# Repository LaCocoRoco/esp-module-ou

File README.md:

# Operating Unit

Portable operating panel with touch buttons.

## Quick Guide

1. Order PCB by uploading the [Gerber File](pcb/cam/esp-module-ou.zip) to [JLCPCB](https://jlcpcb.com/).
2. Order Parts by uploading the [BOM File](pcb/bom/esp-module-ou.csv) to [LCSC](https://www.lcsc.com/bom).
3. Build PCB by placing components as visualized in the [BOM Viewer](https://htmlpreview.github.io/?https://github.com/LaCocoRoco/esp-module-ou/blob/main/pcb/bom/esp-module-ou.html).
4. Download & Install [Git](https://git-scm.com/), [CP210x Driver](https://www.silabs.com/developers/usb-to-uart-bridge-vcp-drivers?tab=downloads) and [VSCode](https://code.visualstudio.com/) with [PlatformIO](https://platformio.org/) Extension.
5. Clone the Repository `git clone --recursive https://github.com/LaCocoRoco/esp-module-ou.git`.
6. With PlatformIO `Upload Filsystem Image` & `Upload & Monitor ` to your board.

## Module Modes

Modes can be changed by pressing the mode button.  
An audio signal will provide feedback for the active mode.  
Holding the mode button for more than two seconds will clear the module.

### Low Power Mode

- Feedback with one audio signal
- All web functionality is disabled
- Device will enter deep sleep when inactive
- Battery lifetime of several months

### Hybrid Mode

- Feedback with two audio signals
- All web functionality is disabled
- Device will enter deep sleep when battery voltage is below 3.8V
- Battery lifetime of several days

### Web Mode

- Feedback with three audio signals
- All web functionality is enabled
- Battery lifetime of several hours

## Importend

All modules have three different modes: Web Mode, Hybrid Mode, and Low Power Mode.  
The Wi-Fi can be configured as either Access Point or Station Mode.  
However, due to the use of the EspNow protocol for communication, there are some restrictions.

### Modules Set Up as Access Points (Default):

- All modes work without any restrictions.

### Modules Set Up in Station Mode:

- Web Mode works without any restrictions.
- Low Power Mode and Hybrid Mode only work if the Wi-Fi network is set to a **fixed channel**.

### Modules Set Up in Access Point or Station Mode:

- All modes only work if the Wi-Fi network is set to **channel 1**.

## Explanation

The main goal of this project was to avoid reliance on any infrastructure. For configuration, neither an application nor an existing Wi-Fi network is necessary. All modules can be accessed via the corresponding SSID in Access Point Mode or via hostname in Station Mode. However, there are some trade-offs:

To reduce power consumption in Low Power Mode, the module does not establish a direct network connection. It only broadcasts data to the specified receiver. In Station Mode, the network may change the Wi-Fi channel occasionally. Connecting to the network to receive this information would significantly increase uptime.

An alternative approach to this problem would be to scan for the receiver and request the channel. However, this has additional drawbacks:

- Scanning for this information takes some time (though less compared to connecting to a Wi-Fi network).
- It is difficult to distinguish whether a transmission failure is due to the wrong channel or a general network issue.
- Continuously requesting this information until a response is received would quickly add to the uptime and increase power consumption.

This is the reason why the relevant points must be considered mentioned in the [Importand](#importend) section.

## Reference

- [VSCode](https://code.visualstudio.com/) - Lightweight code editor.
- [PlatformIO](https://platformio.org/) - Embedded software development gateway.
- [Autodesk Fusion 360](https://www.autodesk.com/products/fusion-360) - Design and manufacturing software for CAD, CAM, CAE, and PCB.
- [Autodesk Eagle](https://www.autodesk.com/products/eagle) - Electronic design automation software for printed circuit boards.
- [JLCPCB](https://jlcpcb.com/) - Reasonably priced PCB manufacturer.
- [LCSC](https://www.lcsc.com/) - Supplier for a wide selection of electronic components.
- [CP210x Driver](https://www.silabs.com/developers/usb-to-uart-bridge-vcp-drivers?tab=downloads) - USB to UART Driver for uploading codebase.
- [InteractiveHtmlBom](https://github.com/openscopeproject/InteractiveHtmlBom) - Bill of materials listing to visually search for components and their placements.

## Preview

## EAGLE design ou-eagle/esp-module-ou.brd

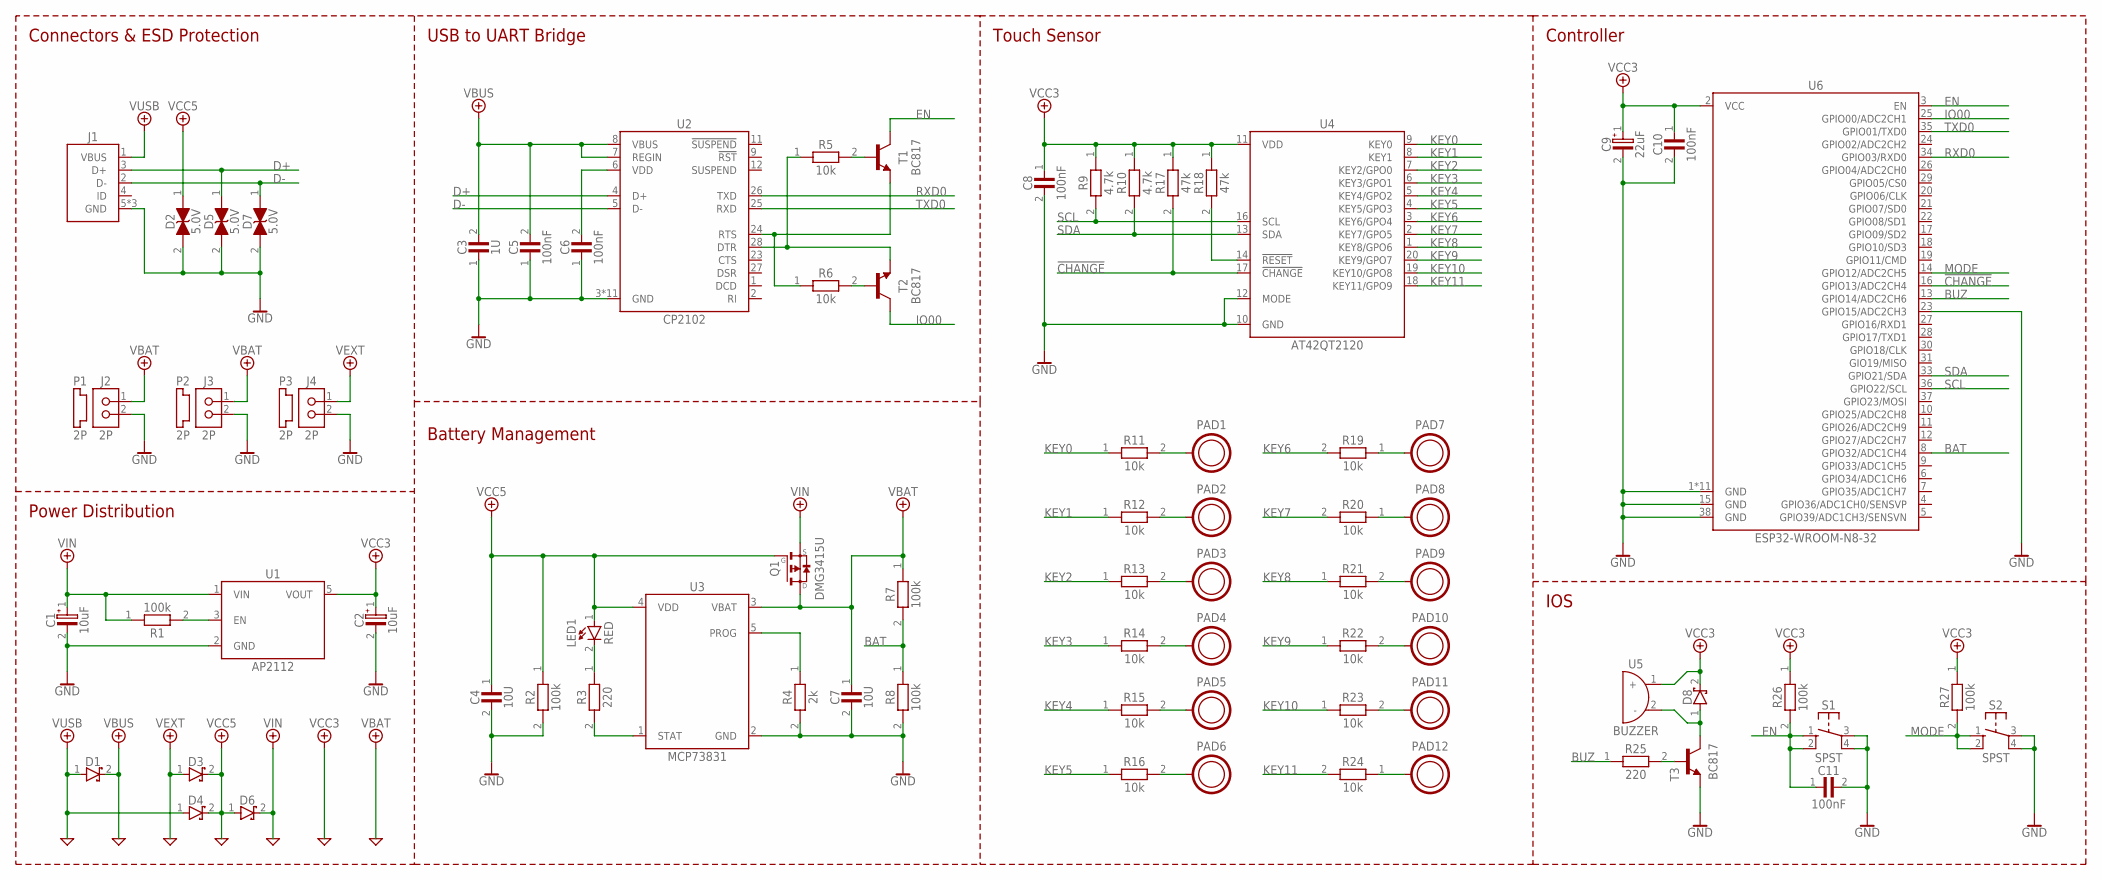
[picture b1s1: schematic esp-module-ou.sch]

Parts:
C1, C2: 10uF; I1206-M3216-D
C3: 1U; I0805-M2012-C
C4, C7: 10U; I0805-M2012-C
C5, C6, C8, C10, C11: 100nF; I0805-M2012-C
C9: 22uF; I1206-M3216-D
D1, D3, D4, D6, D8: 30V; SOD-323
D2, D5, D7: 5.0V; SOD-523
J1: USB-A-MICRO-TOP
J2, J3, J4: 2P; JST-S2B-PH-SM4-TB
LED1: RED; I0805-M2012-D
P1, P2, P3: 2P; CONNECTOR-DEFAULT
PAD1, PAD2, PAD3, PAD4, PAD5, PAD6, PAD7, PAD8, PAD9, PAD10, PAD11, PAD12: QTOUCH
Q1: DMG3415U; SOT-23-3
R1, R2, R7, R8, R26, R27: 100k; I0805-M2012-R
R3, R25: 220; I0805-M2012-R
R4: 2k; I0805-M2012-R
R5, R6, R11, R12, R13, R14, R15, R16, R19, R20, R21, R22, R23, R24: 10k; I0805-M2012-R
R9, R10: 4.7k; I0805-M2012-R
R17, R18: 47k; I0805-M2012-R
S1, S2: SPST; SMD-SW-4
T1, T2, T3: BC817; SOT-23-3
U1: AP2112; SOT-25-5
U2: CP2102; QFN-28
U3: MCP73831; SOT-23-5
U4: AT42QT2120; TSSOP-20
U5: BUZZER; SMD-BUZZER
U6: ESP32-WROOM-N8-32; ESP32-WROOM-32

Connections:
!CHANGE: R17.2, U4.17 (!CHANGE), U6.16 (GPIO13/ADC2CH4)
!RESET: R18.2, U4.14 (!RESET)
APEN: R1.2, U1.3 (EN)
BAT: R7.2, R8.1, U6.8 (GPIO32/ADC1CH4)
BUZ: R25.1, U6.13 (GPIO14/ADC2CH6)
BZB: R25.2, T3.1 (B)
BZC: D8.1 (A), T3.3 (C), U5.2 (-)
D+: D5.1 (A), J1.3 (D+), U2.4 (D+)
D-: D7.1 (A), J1.2 (D-), U2.5 (D-)
DTR: R5.1, T2.2 (E), U2.28 (DTR)
DTRT: R5.2, T1.1 (B)
EN: C11.1, R26.2, S1.1, S1.2, T1.3 (C), U6.3 (EN)
GND: C1.2 (-), C2.2 (-), C3.1, C4.2, C5.1, C6.1, C7.2, C8.2, C9.2 (-), C10.2, C11.2, D2.2 (C), D5.2 (C), D7.2 (C), J1.5 (GND), J1.6 (GND), J1.7 (GND), J2.2, J3.2, J4.2, R2.2, R4.2, R8.2, S1.3, S1.4, S2.3, S2.4, T3.2 (E), U1.2 (GND), U2.3 (GND), U2.29 (GND), U2.30 (GND), U2.31 (GND), U2.32 (GND), U2.33 (GND), U2.34 (GND), U2.35 (GND), U2.36 (GND), U2.37 (GND), U2.38 (GND), U3.2 (GND), U4.10 (GND), U4.12 (MODE), U6.1 (GND), U6.15 (GND), U6.23 (GPIO15/ADC2CH3), U6.38 (GND), U6.39 (GND), U6.40 (GND), U6.41 (GND), U6.42 (GND), U6.43 (GND), U6.44 (GND), U6.45 (GND), U6.46 (GND), U6.47 (GND), U6.48 (GND)
IO00: T2.3 (C), U6.25 (GPIO00/ADC2CH1)
KEY0: R11.1, U4.9 (KEY0)
KEY1: R12.1, U4.8 (KEY1)
KEY2: R13.1, U4.7 (KEY2/GPO0)
KEY3: R14.1, U4.6 (KEY3/GPO1)
KEY4: R15.1, U4.5 (KEY4/GPO2)
KEY5: R16.1, U4.4 (KEY5/GPO3)
KEY6: R19.2, U4.3 (KEY6/GPO4)
KEY7: R20.2, U4.2 (KEY7/GPO5)
KEY8: R21.1, U4.1 (KEY8/GPO6)
KEY9: R22.1, U4.20 (KEY9/GPO7)
KEY10: R23.1, U4.19 (KEY10/GPO8)
KEY11: R24.2, U4.18 (KEY11/GPO9)
MODE: R27.2, S2.1, S2.2, U6.14 (GPIO12/ADC2CH5)
PAD00: PAD1.1, R11.2
PAD01: PAD2.1, R12.2
PAD02: PAD3.1, R13.2
PAD03: PAD4.1, R14.2
PAD04: PAD5.1, R15.2
PAD05: PAD6.1, R16.2
PAD06: PAD7.1, R19.1
PAD07: PAD8.1, R20.1
PAD08: PAD9.1, R21.2
PAD09: PAD10.1, R22.2
PAD10: PAD11.1, R23.2
PAD11: PAD12.1, R24.1
PROG: R4.1, U3.5 (PROG)
RTS: R6.1, T1.2 (E), U2.24 (RTS)
RTST: R6.2, T2.1 (B)
RXD0: U2.26 (TXD), U6.34 (GPIO03/RXD0)
SCL: R9.2, U4.16 (SCL), U6.36 (GPIO22/SCL)
SDA: R10.2, U4.13 (SDA), U6.33 (GPIO21/SDA)
STAT: R3.2, U3.1 (STAT)
STATLED: LED1.2 (C), R3.1
TXD0: U2.25 (RXD), U6.35 (GPIO01/TXD0)
VBAT: C7.1, J2.1, J3.1, Q1.3 (D), R7.1, U3.3 (VBAT)
VBUS: C3.2, C5.2, D1.2 (C), U2.7 (REGIN), U2.8 (VBUS)
VCC3: C2.1 (+), C8.1, C9.1 (+), C10.1, D8.2 (C), R9.1, R10.1, R17.1, R18.1, R26.1, R27.1, U1.5 (VOUT), U4.11 (VDD), U5.1 (+), U6.2 (VCC)
VCC5: C4.1, D2.1 (A), D3.2 (C), D4.2 (C), D6.1 (A), LED1.1 (A), Q1.1 (G), R2.1, U3.4 (VDD)
VDD: C6.2, U2.6 (VDD)
VEXT: D3.1 (A), J4.1
VIN: C1.1 (+), D6.2 (C), Q1.2 (S), R1.1, U1.1 (VIN)
VUSB: D1.1 (A), D4.1 (A), J1.1 (VBUS)

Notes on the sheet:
Power Distribution
Battery Management
Connectors & ESD Protection
USB to UART Bridge
Touch Sensor
Controller
IOS

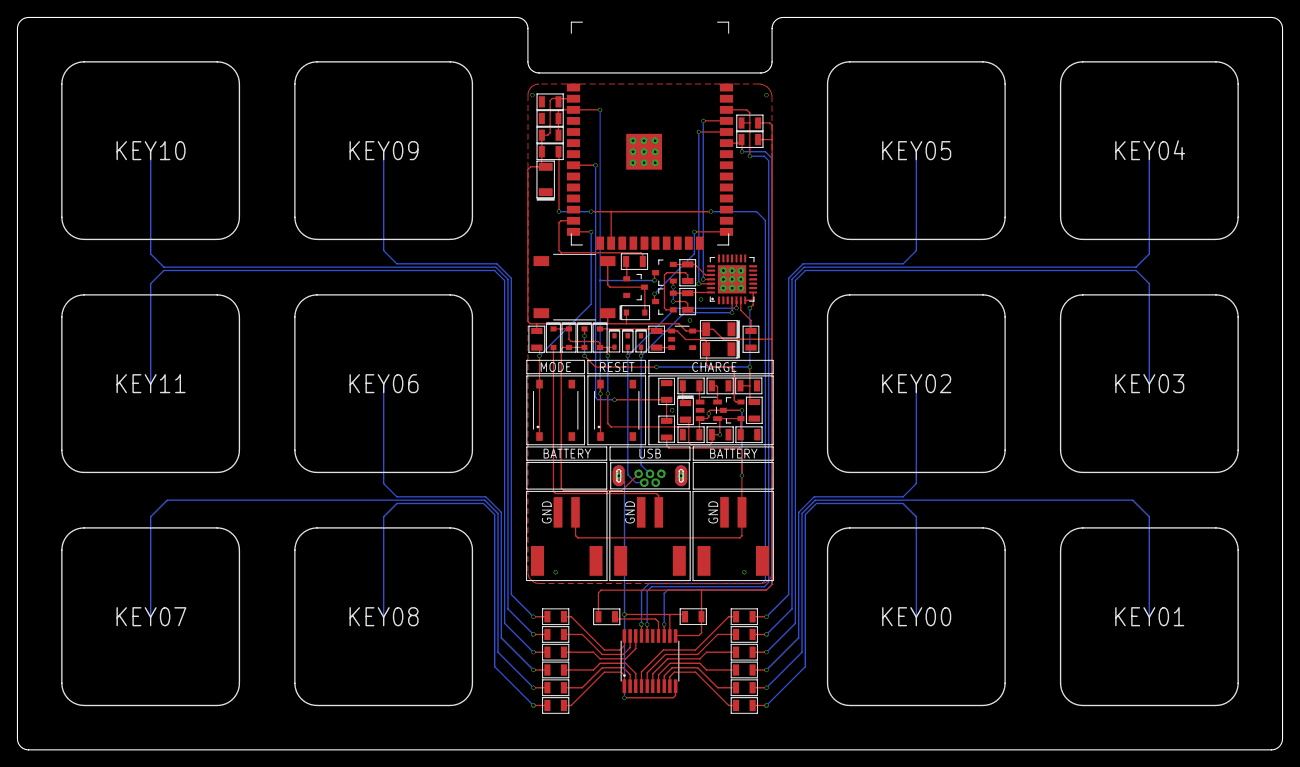
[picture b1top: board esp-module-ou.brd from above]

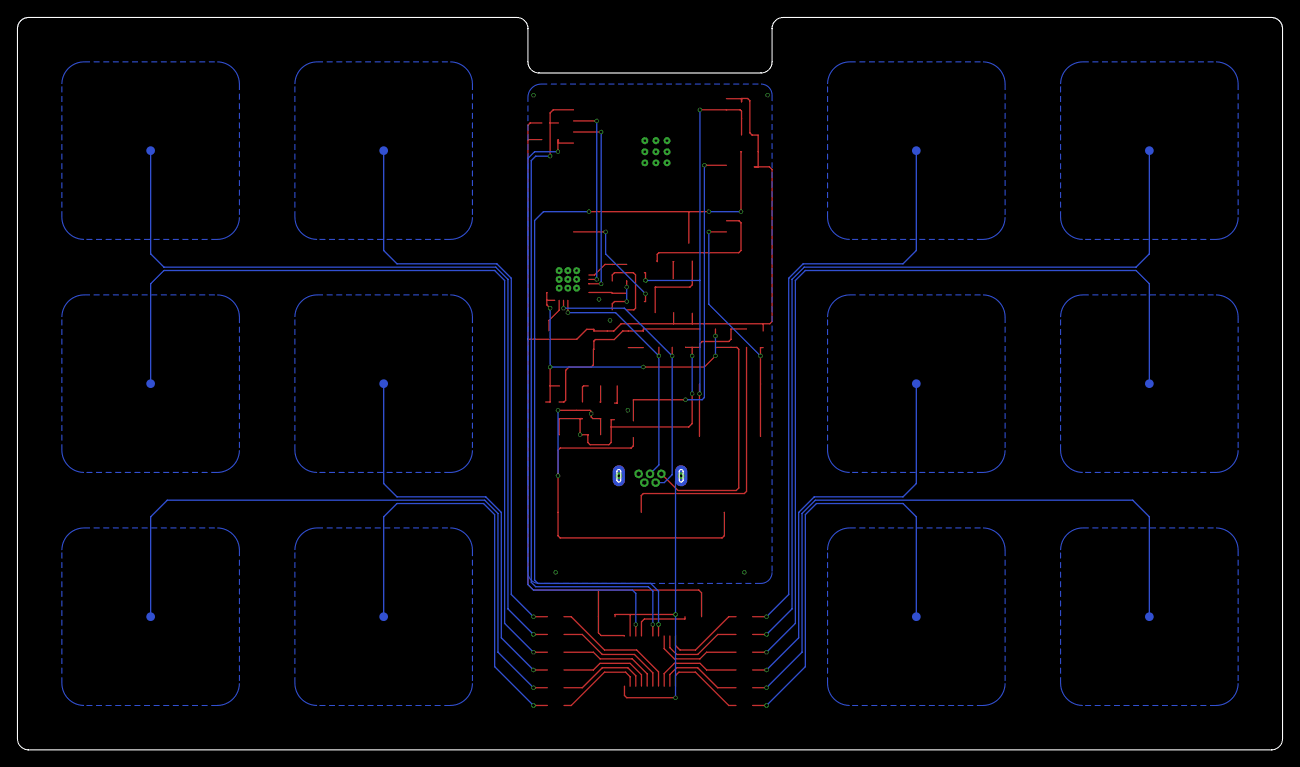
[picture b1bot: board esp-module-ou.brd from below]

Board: 2 copper layers, 144.8 x 83.8 mm, 78 parts (12 on the bottom side), 56 nets.
